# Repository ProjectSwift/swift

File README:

Project Swift : www.projectswift.co.uk
--------------------------------------

This is the firmware for the Swift flight computer.

--- AUTHORS ---

Nigel Smart <nigel@projectswift.co.uk>
Philip Heron <phil@sanslogic.co.uk>

--- PIN USAGE ---

PA0: RTTY space
PA1: RTTY mark
PA2: RTTY enable
PA3: DS1821 1-wire temperature sensors
PA4: AX.25 enable
PA5: VBATT_SENSE, VCC / 10 (ADC)

PB7: Status LED

PC0: BMP085 Pressure sensor (I2C SCL)
PC1: BMP085 Pressure sensor (I2C SDA)

PD0: SSDV RX (UART0)
PD1: SSDV TX (UART0)
PD2: GPS RX (UART1)
PD3: GPS TX (UART1)
PD7: AX.25 audio (PWM)

--- TIMER USAGE ---

Timer0 is used for the RTTY modem
Timer2 is used for the AX.25 modem

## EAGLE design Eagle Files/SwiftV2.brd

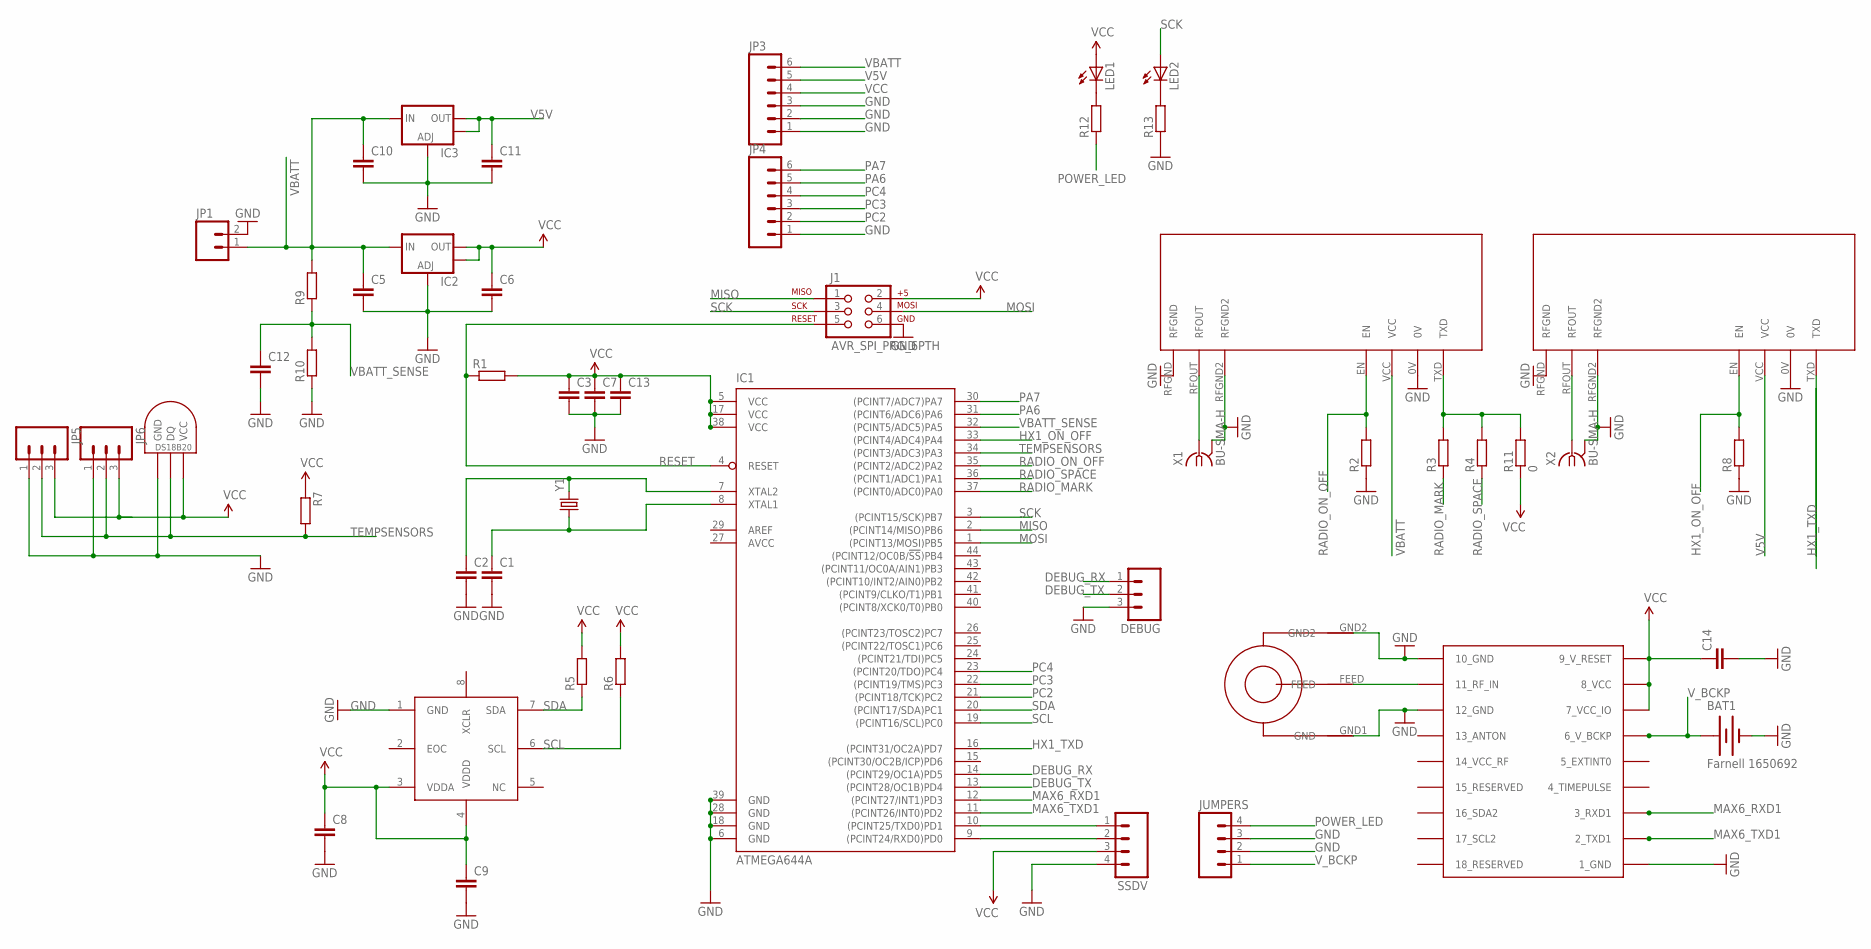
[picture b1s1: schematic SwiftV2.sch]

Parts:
BAT1: Farnell 1650692; BATTCON_12MM
C1, C2, C3, C5, C6, C7, C8, C9, C10, C11, C12, C13, C14: C-EUC0805; C0805
DEBUG: M03PTH; 1X03
IC1: ATMEGA644A; TQFP44
IC2, IC3: V_REG_LM1117SOT223; SOT223
J1: AVR_SPI_PRG_6PTH; 2X3
JP1: M02JST-PTH-2; JST-2-PTH
JP3, JP4: M06SIP; 1X06
JP5, JP6: M03JST-PTH; JST-3-PTH
JUMPERS: M04PTH; 1X04
LED1, LED2: LED0603; LED-0603
R1, R2, R3, R4, R5, R6, R7, R8, R9, R10, R12, R13: R-EU_R0805; R0805
R11: 0; R0805
SSDV: M04PTH; 1X04
TEMPINT: DS1821; DS18B20_SOIC
U$1: BMP085
U$2: NTX2
U$3: SARANTEL-SR1202
U$4: UBLOX_MAX-6
U$5: RADIOMETRIX-HX1
X1, X2: BU-SMA-H
Y1: CRYSTALSMD; HC49UP

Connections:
AVCC: IC1.27 (AVCC)
DEBUG_RX: DEBUG.1, IC1.14 ((PCINT29/OC1A)PD5)
DEBUG_TX: DEBUG.2, IC1.13 ((PCINT28/OC1B)PD4)
GND: BAT1.GND (-), C1.2, C2.2, C3.2, C5.2, C6.2, C7.2, C8.2, C9.2, C10.2, C11.2, C12.2, C13.2, C14.2, DEBUG.3, IC1.6 (GND), IC1.18 (GND), IC1.28 (GND), IC1.39 (GND), IC2.1 (ADJ), IC3.1 (ADJ), J1.6, JP1.2, JP3.1, JP3.2, JP3.3, JP4.1, JP5.1, JP6.1, JUMPERS.2, JUMPERS.3, R2.1, R8.1, R10.1, R13.1, SSDV.4, TEMPINT.GND, U$1.1 (GND), U$2.0V, U$2.RFGND, U$2.RFGND2, U$3.GND1 (GND), U$3.GND2, U$4.1_GND, U$4.10_GND, U$4.12_GND, U$5.0V, U$5.RFGND, U$5.RFGND2, X1.2 (GND), X1.3 (GND), X1.4 (GND), X1.5 (GND), X2.2 (GND), X2.3 (GND), X2.4 (GND), X2.5 (GND)
HX1_ON_OFF: IC1.33 ((PCINT4/ADC4)PA4), R8.2, U$5.EN
HX1_TXD: IC1.16 ((PCINT31/OC2A)PD7), U$5.TXD
MAX6_RXD1: IC1.12 ((PCINT27/INT1)PD3), U$4.3_RXD1
MAX6_TXD1: IC1.11 ((PCINT26/INT0)PD2), U$4.2_TXD1
MISO: IC1.2 ((PCINT14/MISO)PB6), J1.1
MOSI: IC1.1 ((PCINT13/MOSI)PB5), J1.4
unnamed: C2.1, IC1.7 (XTAL2), Y1.2
unnamed: C1.1, IC1.8 (XTAL1), Y1.1
unnamed: U$2.RFOUT, X1.1
unnamed: LED1.C, R12.2
unnamed: U$5.RFOUT, X2.1
unnamed: U$3.FEED, U$4.11_RF_IN
unnamed: R3.2, R4.2, R11.2, U$2.TXD
unnamed: LED2.C, R13.2
PA6: IC1.31 ((PCINT6/ADC6)PA6), JP4.5
PA7: IC1.30 ((PCINT7/ADC7)PA7), JP4.6
PC2: IC1.21 ((PCINT18/TCK)PC2), JP4.2
PC3: IC1.22 ((PCINT19/TMS)PC3), JP4.3
PC4: IC1.23 ((PCINT20/TDO)PC4), JP4.4
POWER_LED: JUMPERS.4, R12.1
RADIO_MARK: IC1.37 ((PCINT0/ADC0)PA0), R3.1
RADIO_ON_OFF: IC1.35 ((PCINT2/ADC2)PA2), R2.2, U$2.EN
RADIO_SPACE: IC1.36 ((PCINT1/ADC1)PA1), R4.1
RESET: IC1.4 (RESET), J1.5, R1.1
RXD0: IC1.9 ((PCINT24/RXD0)PD0), SSDV.2
SCK: IC1.3 ((PCINT15/SCK)PB7), J1.3, LED2.A
SCL: IC1.19 ((PCINT16/SCL)PC0), R6.1, U$1.6 (SCL)
SDA: IC1.20 ((PCINT17/SDA)PC1), R5.1, U$1.7 (SDA)
TEMPSENSORS: IC1.34 ((PCINT3/ADC3)PA3), JP5.2, JP6.2, R7.2, TEMPINT.DQ
TXD0: IC1.10 ((PCINT25/TXD0)PD1), SSDV.1
V5V: C11.1, IC3.2 (OUT), IC3.4 (OUT), JP3.5, U$5.VCC
VBATT: C5.1, C10.1, IC2.3 (IN), IC3.3 (IN), JP1.1, JP3.6, R9.2, U$2.VCC
VBATT_SENSE: C12.1, IC1.32 ((PCINT5/ADC5)PA5), R9.1, R10.2
VCC: C3.1, C6.1, C7.1, C8.1, C9.1, C13.1, C14.1, IC1.5 (VCC), IC1.17 (VCC), IC1.38 (VCC), IC2.2 (OUT), IC2.4 (OUT), J1.2, JP3.4, JP5.3, JP6.3, LED1.A, R1.2, R5.2, R6.2, R7.1, R11.1, SSDV.3, TEMPINT.VCC, U$1.3 (VDDA), U$1.4 (VDDD), U$4.7_VCC_IO, U$4.8_VCC, U$4.9_V_RESET
V_BCKP: BAT1.PWR@1 (+), JUMPERS.1, U$4.6_V_BCKP

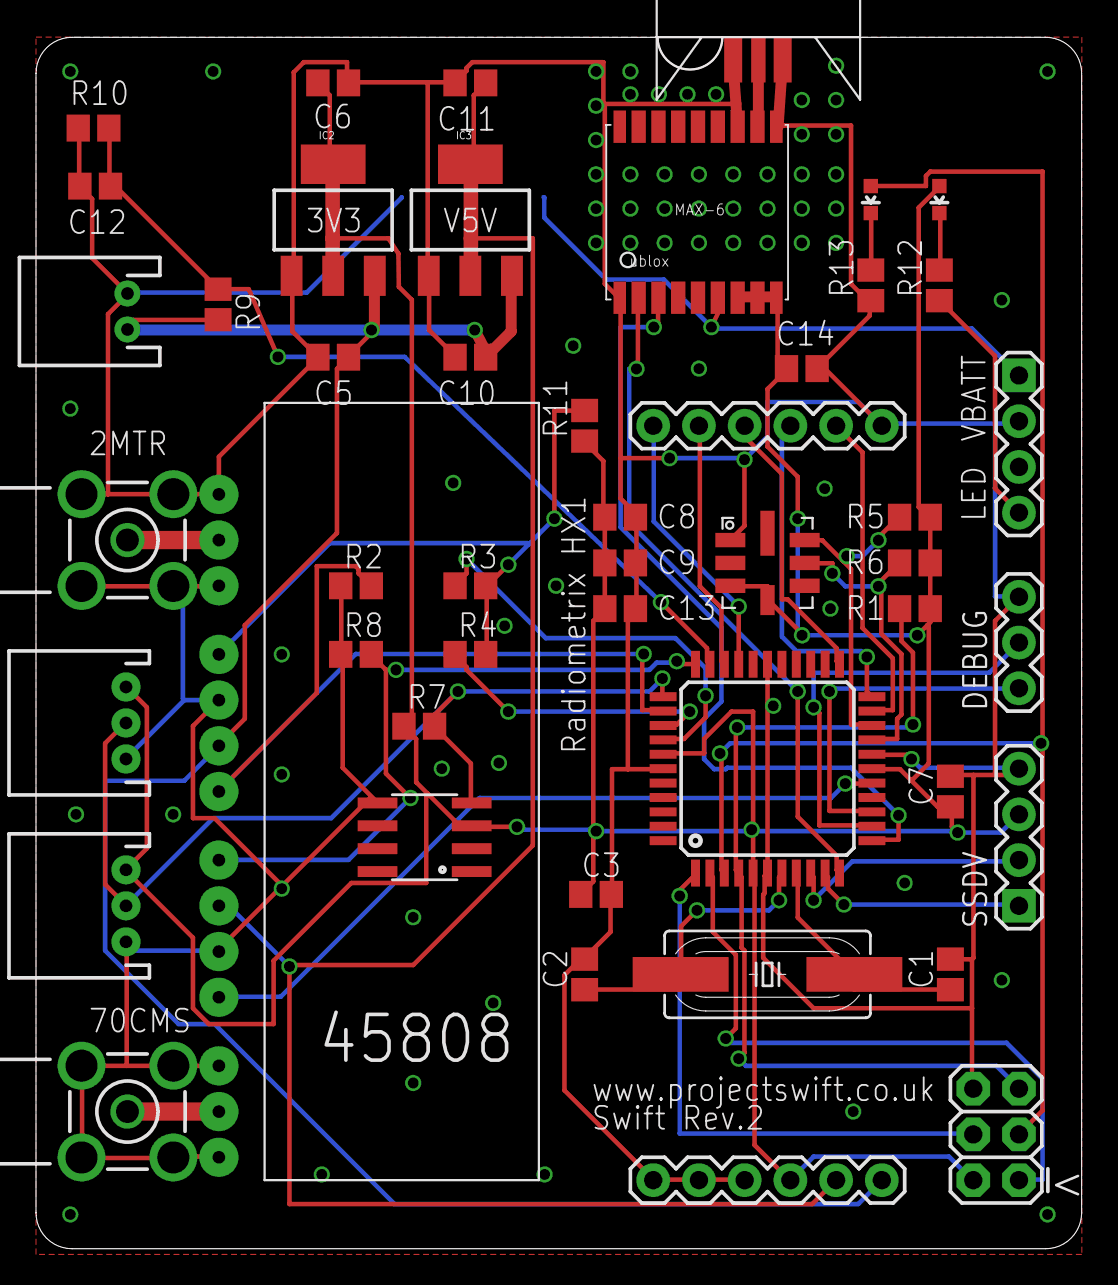
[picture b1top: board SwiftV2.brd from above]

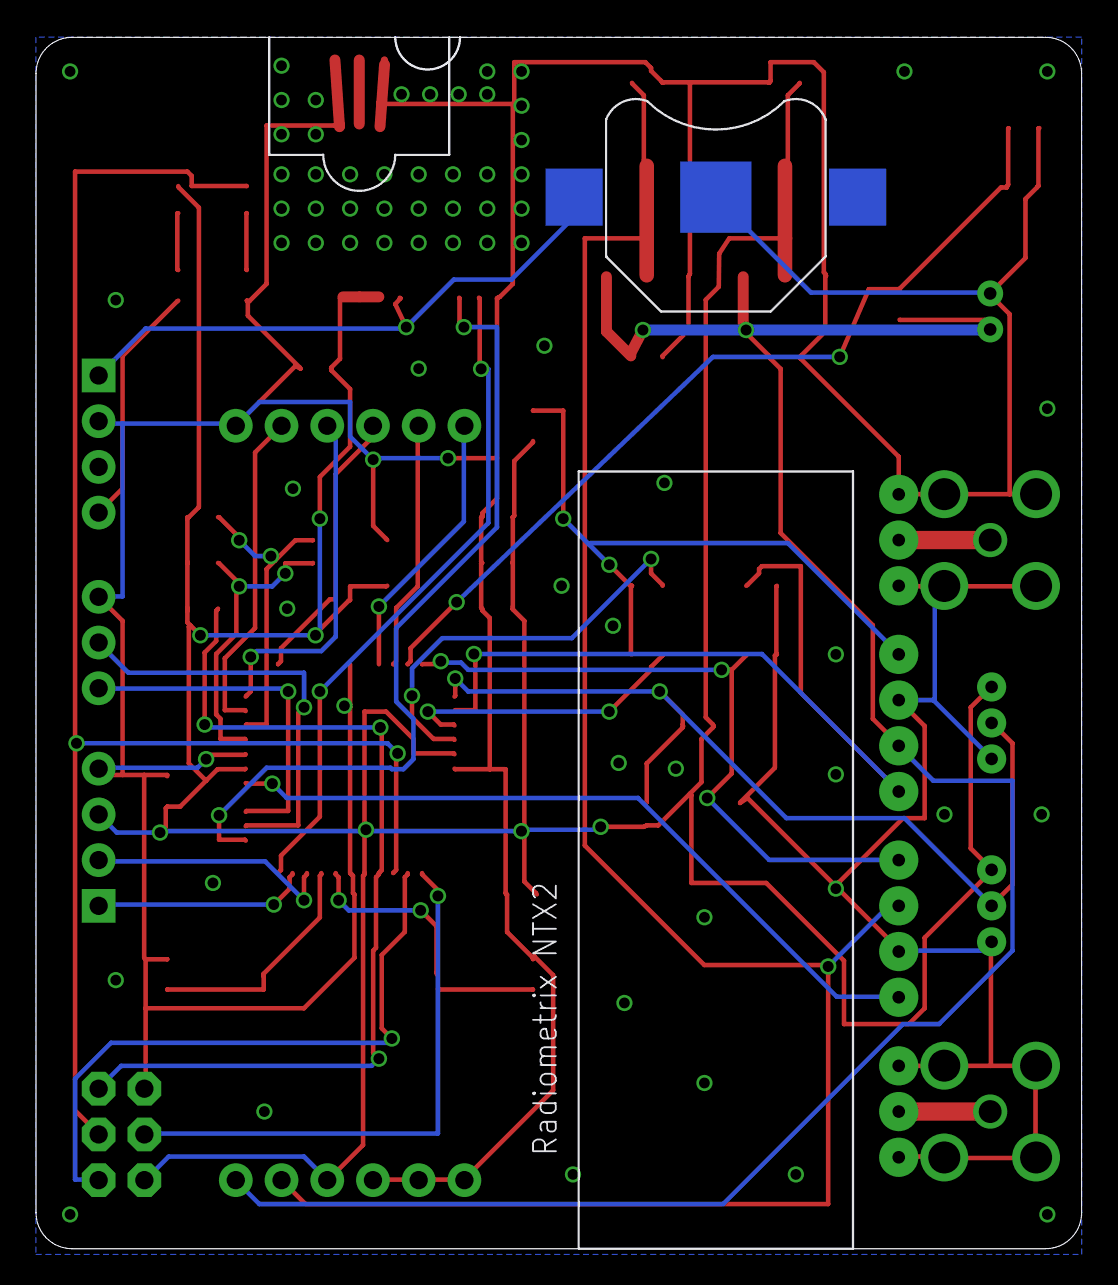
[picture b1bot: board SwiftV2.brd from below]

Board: 2 copper layers, 58.1 x 67.3 mm, 50 parts (2 on the bottom side), 38 nets.

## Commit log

2012-03-21 Using the GPL3 license
2012-03-26 Add .gitignore
2012-03-26 Add RTTY modem functions and a basic test program
2012-03-26 Enable RTTY radio on startup, and swap MARK and SPACE to correct pins
2012-03-28 Added gps parser
2012-03-28 Some small updates to GPS code
2012-03-31 Updated gps parser
2012-04-01 Tidy up the UBX packet code
2012-04-01 Some more GPS tidyups
2012-04-01 Added early version of GPS GeoFence
2012-04-02 Updated Geofence Co-Ordinates
2012-04-02 Transmit proper GPS values over RTTY, and add CRC16 checksum
2012-04-02 Updated README with pin and timer descriptions
2012-04-02 modified geofence from float to int32_t
2012-04-02 removed a leading 0 from geofence coordinates
2012-04-03 Added Eagle Files For Rev 2
2012-04-03 Tidied up rev2 eagle files
2012-04-03 Add authors contact details
2012-04-03 geofence test code implemented into swift.c
2012-04-04 Fixed a typo in swift.c
2012-04-05 Updated Credits
2012-04-07 Small tidyups
2012-04-07 More tidyups
2012-04-07 Put geofence into PROGMEM
2012-04-07 Add a geofence status flag to the RTTY telemetry
2012-04-08 Initial ax.25/APRS support
2012-04-08 Static function is static
2012-04-08 Tweak the preamble and rest times
2012-04-08 Use the optimised CRC16 function from avr-libc
2012-04-08 Add code to read the battery voltage
2012-04-10 Add compressed telemetry. Just supply voltage for now
2012-04-15 Properly format the callsign in message packets
2012-04-15 Add code to search for and query a DS18B20 temperature sensor
2012-04-15 Make room for the null terminator when preparing callsign string
2012-04-15 Typo
2012-04-15 Declare the msg variable static. Fixes bug where first packet of a group was corrupt.
2012-04-16 Ahem, nothing to see here
2012-04-16 Document delays a bit better
2012-05-04 Rename temperature sensor files
2012-05-04 Fixes to the 1-wire code and temperature conversions for DS18S20 sensors
2012-05-04 Added temp sensor to telemetry.
2012-05-07 First attempt at a BMP085 library
2012-05-10 Fetch calibration values automatically if not already loaded
2012-05-10 Add pressure to telemetry data
2012-05-14 Fixes to 1-Wire to enable multiple sensors.
2012-05-14 Deleted 1
2012-08-16 Tidyup
2012-09-29 Add the timer/timeout functions
2012-09-30 Make the UBX parser not suck as much
2012-09-30 Some more tidyup
2012-09-30 Add the SSDV encoder files
2012-09-30 Add DOP functions, as well as other tidyups. Closes #1
2012-10-19 Read the current navmode settings, rather than using a static example
2012-10-19 Set the nav-mode every 10 strings
2012-10-19 Don't set the nav-mode if it's already the supplied value
2012-10-19 Document the navmode
2013-02-23 Put the sine table into PROGMEM
2013-02-23 Update C328 functions to use new timeout code
2013-02-23 Tidy up CRC generation
2013-03-12 Use program memory version of snprintf()
2013-03-12 Print avr-size report after linking
2013-03-12 Clean up the Makefile a bit
2013-03-12 Add code to transmit SSDV packets
2013-03-12 Send C328 camera command to finish previous image before opening
2013-03-12 Enclose SSDV and APRS init functions in #ifdefs
